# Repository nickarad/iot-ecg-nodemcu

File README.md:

# Clintelli

Clintelli stands for Clinical Intelligence and is a platform that leverages Artificial Intelligence and wearable IoT technologies to monitor clinical data and improve patient care.

- [Hackaday 2019 Project](https://hackaday.io/project/165310-clintelli)
- [Documentation](https://nickarad.github.io/clintelli/)

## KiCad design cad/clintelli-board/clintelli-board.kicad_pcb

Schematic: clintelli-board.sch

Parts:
C1: 1.5nF
C3, C9: 100nF; C_0805
C4, C5: 10pF; C_0805
C6, C7, C8: 1uF; C_0805
D1: LED; LED_0805
J1: AudioJack4_Ground
J2, J3: AudioJack3_Ground
L1: 22uH
P1, P2, P3, P4: CONN_01X01; MountingHole_2.2mm_M2_Pad
R1: 1M
R2: 1k; C_0805
SW1: SW_PUSH; SW_SPST_PTS830
U1: VDD; SOT-23-5
U2: ESP32-WROOM-32
U3: ADS1298xPAG; TQFP-64_10x10mm_P0.5mm
U4: ATECC608A-MAHDA; DFN-8-1EP_3x2mm_P0.5mm_EP1.3x1.5mm
U5: STM32F302RETx; LQFP-64_10x10mm_P0.5mm
Y1: 32MHz; FA238-4pin_3.2x2.5mm_Offset

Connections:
+3V3: C7.2, C8.1, C9.1, L1.2, R2.1, U1.5 (VOUT), U2.2 (VDD), U2.3 (EN), U3.48 (DVDD), U3.50 (DVDD), U4.8 (VCC), U5.1 (VBAT), U5.19 (VDD), U5.32 (VDD), U5.48 (VDD), U5.64 (VDD)
/C1: J2.S
/C2: J2.R
/C3: J2.T
/C4: J3.S
/C5: J3.R
/C6: J3.T
/I2C_SCL: U4.6 (SCL), U5.42 (PA9)
/I2C_SDA: U4.5 (SDA), U5.43 (PA10)
/LA: J1.R2, U3.11 (IN3N), U3.16 (IN1P)
/LL: J1.T, U3.12 (IN3P), U3.14 (IN2P)
/OSC_IN: C4.2, U5.5 (PF0), Y1.1
/OSC_OUT: C5.2, U5.6 (PF1), Y1.3
/RA: J1.R1, U3.13 (IN2N), U3.15 (IN1N)
/RESET: C3.2, SW1.1, U5.7 (NRST)
/RL: C1.2, J1.S, R1.2, U3.61 (RLDINV)
/RLDINV: C1.1, R1.1, U3.63 (RLDOUT)
/SPI1_MISO: U3.43 (DOUT), U5.22 (PA6)
/SPI1_MOSI: U3.34 (DIN), U5.23 (PA7)
/SPI1_NSS: U3.39 (~CS), U5.20 (PA4)
/SPI1_SCK: U3.40 (SCLK), U5.21 (PA5)
/SPI3_MISO: U2.14 (IO12), U5.52 (PC11)
/SPI3_MOSI: U2.16 (IO13), U5.53 (PC12)
/SPI3_NSS: U2.23 (IO15), U5.50 (PA15)
/SPI3_SCK: U2.13 (IO14), U5.51 (PC10)
GND: C3.1, C4.1, C5.1, C6.1, C7.1, C8.2, C9.2, D1.1 (K), P1.1, P2.1, P3.1, P4.1, SW1.2, U1.2 (GND), U2.1 (GND), U2.15 (GND), U2.38 (GND), U3.20 (AVSS), U3.23 (AVSS), U3.32 (AVSS), U3.33 (DGND), U3.49 (DGND), U3.51 (DGND), U3.53 (AVSS1), U3.57 (AVSS), U3.58 (AVSS), U4.4 (GND), U5.12 (VSSA), U5.18 (VSS), U5.31 (VSS), U5.47 (VSS), U5.63 (VSS), Y1.2, Y1.4
unnamed: D1.2 (A), R2.2
VCC: C6.2, U1.1 (VIN), U1.3 (EN)
VDDA: L1.1, U3.19 (AVDD), U3.21 (AVDD), U3.22 (AVDD), U3.54 (AVDD1), U3.56 (AVDD), U3.59 (AVDD), U5.13 (VDDA)

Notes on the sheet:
Supply decoupling
External Reset Circuit
Power-ON LED
Step-down Voltage Regulator
PCB Mounting Holes
External Clock 32MHz
Cortex-M4 MCU
ESP32 - WiFi & Bluetooth module
Cryptographic Chip
ECG Module
ECG Leads
3 Lead ECG Connector Limb Leads
Precordial Leads

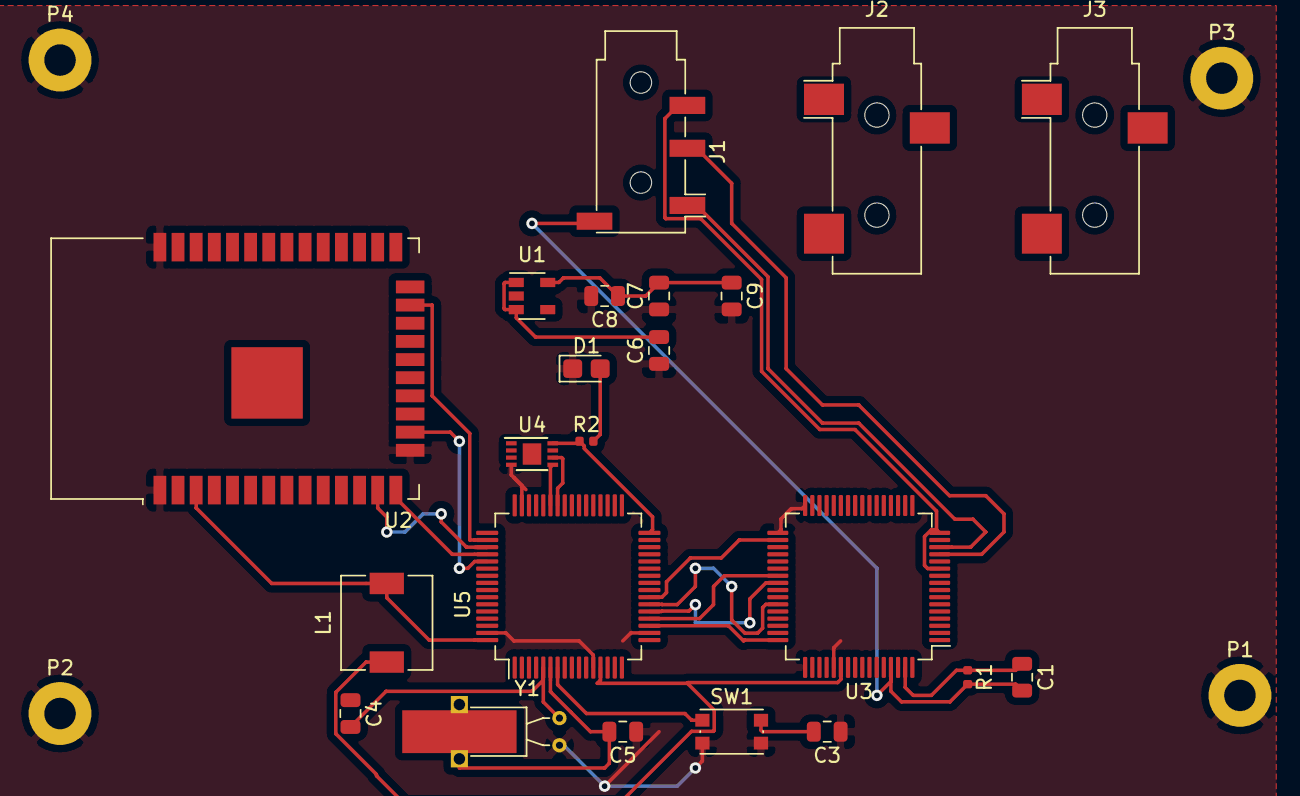
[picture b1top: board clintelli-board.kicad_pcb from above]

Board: 2 copper layers, 26 parts (0 on the bottom side), 23 nets.

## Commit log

2019-07-09 Docsify docs init
2019-07-09 Breadboard Connections
2019-07-09 Add schematic
2019-07-09 Add fritzing files
2019-07-09 Add references for fritzing files
2019-07-09 changed position
2019-07-09 Create and enable sidebar
2019-07-09 Schematics page
2019-07-14 Google IoT Core instructions
2019-07-14 Run RabbitMQ with MQTT enabled via Docker
2019-07-14 Deployment section
2019-07-14 Sample arduino code for MQTT: code from https://funprojects.blog/2018/12/07/rabbitmq-for-iot/
2019-07-14 arduino secret-config
2019-07-14 get temperature and send it as JSON payload
2019-07-14 Python MQTT subscriber test
2019-07-14 Add upload.sh
    Upload arduino code with arduino-cli
    $ bash upload.sh
2019-07-14 Add serial monitor python script
    $ python serial_monitor.py
2019-07-14 Add "python serial_monitor.py" cmd to upload.sh script
2019-07-14 change password
2019-07-15 deleted hostname
2019-07-15 Change baud rate from 9600 to 115200
2019-07-15 Display payload in on_message callback
2019-07-15 Set desired sample rate T=7812microseconds
2019-07-15 ignore arduino compiled files
2019-07-15 Basic setup instructiions with RabbitMQ MQTT
2019-07-15 Real Time Plot Data
2019-07-15 Convert Analog read to Celsius Temperature
2019-07-15 Modify plot
2019-07-15 Fix bug
2019-07-15 fix temperature
2019-07-17 clintelli-board initial schematics
2019-07-17 added coverpage
2019-07-17 clintelli description
2019-07-17 Updated main README file
2019-07-18 Add .vscode/settings.json to .gitignore
2019-07-18 Add getECG function
2019-07-18 Replace temparture with ecg sensor data
2019-07-18 Fix Indents
2019-07-18 Add serial plot.py
2019-07-18 Add serial plot code
2019-07-18 Add ecg plot module
2019-07-18 Add tensorflow model to subscriber
2019-07-20 comments
2019-07-20 clintelli architecture
2019-07-20 deprecate google cloud iot documentation
2019-07-20 Separate schematics into prototpye and custom hardware
2019-07-20 Plot ecg
2019-07-20 Change tempC to ecg
2019-07-20 Change plot parameters
2019-07-21 Schematic changes: - Replaced ESP8266 with ESP32 - Added AudioJack connector - Removed Header pins
2019-07-21 Schematic changes: - Annotations - Cortex M4 wiring - Connected ECG with MCU via SPI - Connected 1 ECG Lead
2019-07-21 Save data to .txt file
2019-07-21 Schematic changes: - 12 ECG Leads connectors
2019-07-21 ESP32 wiring & 1st schematic export
2019-07-21 CLintelli board - first documentation
2019-07-22 MQTT Connection changes: - ESP MAC adress as unique client ID - WillTopic & willMessage - QoS = 2
2019-07-22 added some MQTT references
2019-07-22 added HL7FHIR integration - emr/ehr/phr
2019-07-22 clintelli board datasheets
2019-07-22 First PCB design attempt
2019-07-22 PCB layout second design attempt
2019-07-24 Added Minio and PostgreSQL services
2019-07-25 mechanical cad files - clintelli board house
2019-07-25 Bootstrap android application
2019-08-02 Configure the TICK stack Telegraf, InfluxDB, Chronograf and Kapacitor
2019-08-02 Changes: - Store mac address to string - Reformat message sent to MQTT with JSON format
2019-08-02 Docker-compose changes: - removed private external network - fixed docker-compose errors
2019-08-02 ignore docker local volumes
2019-08-10 enable minio
2019-08-10 commit changes
2019-08-10 fix conflict
2019-08-11 Fix MQTT Qos & Retain in Publisher
2019-08-11 Dpwnload CSV file from chronograf
2019-08-11 Change IP & Fix QoS in Subscriber
2019-08-11 Rename test_sub.py to sub.py
2019-08-11 Add CSV files
2019-08-11 Add predict.py
